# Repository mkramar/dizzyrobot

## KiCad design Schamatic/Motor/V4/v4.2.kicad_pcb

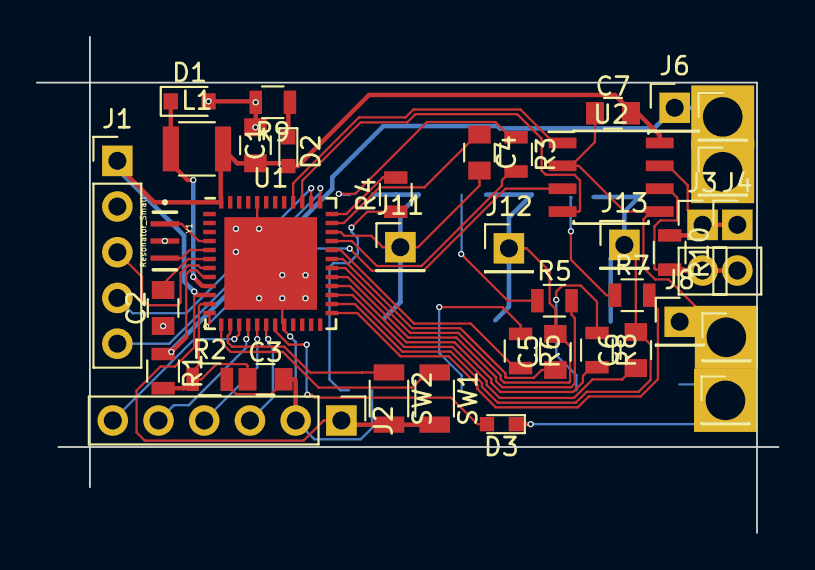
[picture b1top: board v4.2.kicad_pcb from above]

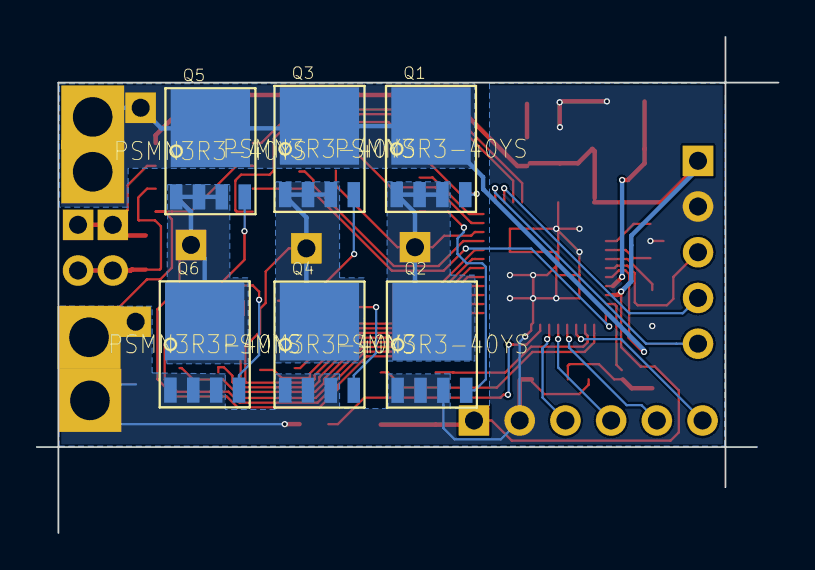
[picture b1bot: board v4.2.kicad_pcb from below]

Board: 4 copper layers, 41.2 x 27.6 mm, 45 parts (6 on the bottom side), 42 nets.

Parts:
C1, C2: 47uF; C_0805
C3, C4, C5, C6, C7: 1uF; C_0805
D1: D; D_0805
D2, D3: LED; LED_0603
J1: SWD; Pin_Header_Straight_1x05_Pitch2.54mm
J2: SPI; Pin_Header_Straight_1x06_Pitch2.54mm
J3, J4: RS485; Pin_Header_Straight_1x02_Pitch2.54mm
J5, J6, J7: 12; Pin_Header_Straight_1x01_Pitch2.54mm
J8, J9, J10: GND; Pin_Header_Straight_1x01_Pitch2.54mm
J11: V; Pin_Header_Straight_1x01_Pitch2.54mm
J12: U; Pin_Header_Straight_1x01_Pitch2.54mm
J13: W; Pin_Header_Straight_1x01_Pitch2.54mm
L1: 22uH; L_1210
Q1, Q2, Q3, Q4, Q5, Q6: PSMN3R3-40YS
R1: 47K; R_0805
R2: 3K; R_0805
R3, R4, R5, R6, R7, R8: 10; R_0805
R9, R10: 120; R_0805
SW1, SW2: SWiTCH; R_1206
U1: STSPIN32F0; QFN-48-1EP_7x7mm_Pitch0.5mm
U2: RS-485; SOIC-8_3.9x4.9mm_Pitch1.27mm
Y1: Resonator_Small; OSC_CSTCE16M0V53-R0

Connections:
+3V3: C1.1, C7.2, D2.2, J1.1, J2.1, L1.2, SW1.2, SW2.2, U1.10, U1.48, U2.8
+12V: J5.1, J6.1, J7.1, Q1.5678, Q3.5678, Q5.5678, R1.1, U1.8
BOOT1: C4.1, U1.35
BOOT2: C5.1, U1.31
BOOT3: C6.1, U1.27
CS: J2.6, U1.15
DE: U1.12, U2.3
Earth: C1.2, C2.1, C3.2, C7.1, D1.2, D3.1, J1.2, J2.2, J8.1, J9.1, J10.1, Q2.1, Q2.2, Q2.3, Q4.1, Q4.2, Q4.3, Q6.1, Q6.2, Q6.3, R2.2, R9.2, U1.20, U1.44, U1.49, U2.2, U2.5, Y1.2
H1: R3.2, U1.33
H2: R5.2, U1.29
H3: R7.2, U1.25
L1: R4.2, U1.36
L2: R6.2, U1.32
L3: R8.2, U1.28
MISO: J2.4, U1.17
MOSI: J2.3, U1.18
NRST: J1.3, U1.7
unnamed: C2.2, U1.6
unnamed: C3.1, R1.2, R2.1, U1.11
unnamed: D1.1, L1.1, U1.9
unnamed: D2.1, R9.1
unnamed: D3.2, U1.19
unnamed: Q1.4, R3.1
unnamed: Q2.4, R4.1
unnamed: Q3.4, R5.1
unnamed: Q4.4, R6.1
unnamed: Q5.4, R7.1
unnamed: Q6.4, R8.1
unnamed: SW1.1, U1.13
unnamed: SW2.1, U1.14
unnamed: U1.4, Y1.1
unnamed: U1.5, Y1.3
O1: C4.2, J11.1, Q1.1, Q1.2, Q1.3, Q2.5678, U1.34
O2: C5.2, J12.1, Q3.1, Q3.2, Q3.3, Q4.5678, U1.30
O3: C6.2, J13.1, Q5.1, Q5.2, Q5.3, Q6.5678, U1.26
RS-A: J3.2, J4.2, R10.2, U2.6
RS-B: J3.1, J4.1, R10.1, U2.7
RX: U1.40, U2.1
SCK: J2.5, U1.16
SWDCLK: J1.4, U1.38
SWDIO: J1.5, U1.37
TX: U1.39, U2.4

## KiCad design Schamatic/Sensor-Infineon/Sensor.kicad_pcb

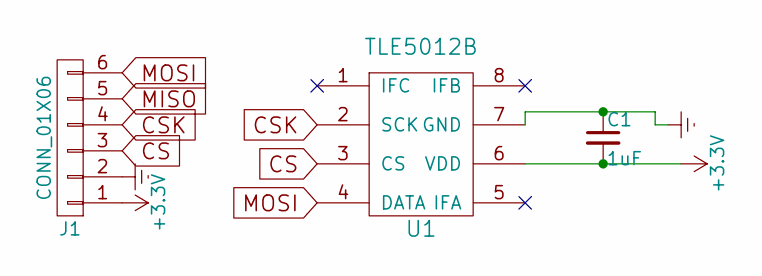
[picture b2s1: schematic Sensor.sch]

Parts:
C1: 1uF; C_0805
J1: CONN_01X06; SPI_CONN
U1: TLE5012B; SOIC-8_3.9x4.9mm_Pitch1.27mm

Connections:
+3V3: C1.2, J1.1, U1.6 (VDD)
CS: J1.3, U1.3 (CS)
CSK: J1.4, U1.2 (SCK)
Earth: C1.1, J1.2, U1.7 (GND)
MISO: J1.5
MOSI: J1.6, U1.4 (DATA)

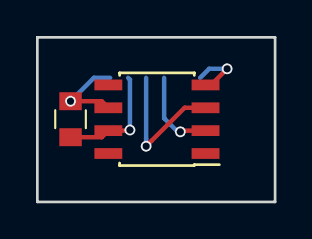
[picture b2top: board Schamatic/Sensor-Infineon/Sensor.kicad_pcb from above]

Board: 2 copper layers, 13.2 x 9.1 mm, 3 parts (1 on the bottom side), 5 nets.

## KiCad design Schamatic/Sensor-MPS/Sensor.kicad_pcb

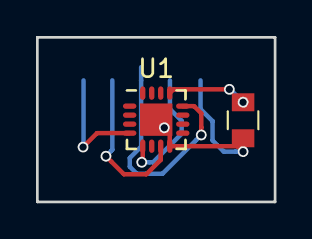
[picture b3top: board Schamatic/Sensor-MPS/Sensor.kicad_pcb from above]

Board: 2 copper layers, 13.2 x 9.1 mm, 3 parts (1 on the bottom side), 6 nets.

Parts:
C1: 1uF; C_0805
J1: CONN_01X06; SPI_cable
U1: MA700; QFN-16-1EP_3x3mm_Pitch0.5mm

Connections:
+3V3: C1.1, J1.6, U1.13
CS: J1.4, U1.5
CSK: J1.3, U1.12
Earth: C1.2, J1.5, U1.8, U1.17
MISO: J1.2, U1.7
MOSI: J1.1, U1.4
